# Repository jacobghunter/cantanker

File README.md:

This is a split wireless keyboard running ZMK with custom PCB and case designs

## Tools/software Used:
- [Ergogen](https://github.com/ergogen/ergogen) for layout and PCB generation as well as DXF files for case design
- [KiCad](https://www.kicad.org/) to wire the PCB
- [FreeCAD](https://www.freecad.org/) for case and plate design
- [ZMK](https://zmk.dev/) for the wireless firmware
- A slightly modified version of [this](https://github.com/AYM1607/zmk-driver-azoteq-iqs5xx) trackpad firmware by AYM1607

A big thank you to all the awesome people who have contributed to these projects, all of this being free and open source is truly amazing!

Its main features are:
- Bluetooth low energy connectivity
- Azotec TPS43 trackpad mounted on the right side
- 5000mAh batteries in each side
- Dual rotary encoders
- Nice! View display
- Low profile with choc v1 switches

## PCB Renders
| Side | Top | Bottom |
| :--- | :---: | :---: |
| **Left Half** |  |  |
| **Right Half** |  |  |

You can find the source FCStd file for the case and plates [here](mechanical/Cantanker_Case_and_Plates.FCStd) and print-ready exports below:
| Part | STLs | STEPs |
| :--- | :--- | :--- |
| **Left Case** | [Download](mechanical/exports/Cantanker_Left_Case.stl) | [Download](mechanical/exports/Cantanker_Left_Case.step) |
| **Right Case** | [Download](mechanical/exports/Cantanker_Right_Case.stl) | [Download](mechanical/exports/Cantanker_Right_Case.step) |
| **Left Plate** | [Download](mechanical/exports/Cantanker_Left_Plate.stl) | [Download](mechanical/exports/Cantanker_Left_Plate.step) |
| **Right Plate** | [Download](mechanical/exports/Cantanker_Right_Plate.stl) | [Download](mechanical/exports/Cantanker_Right_Plate.step) |

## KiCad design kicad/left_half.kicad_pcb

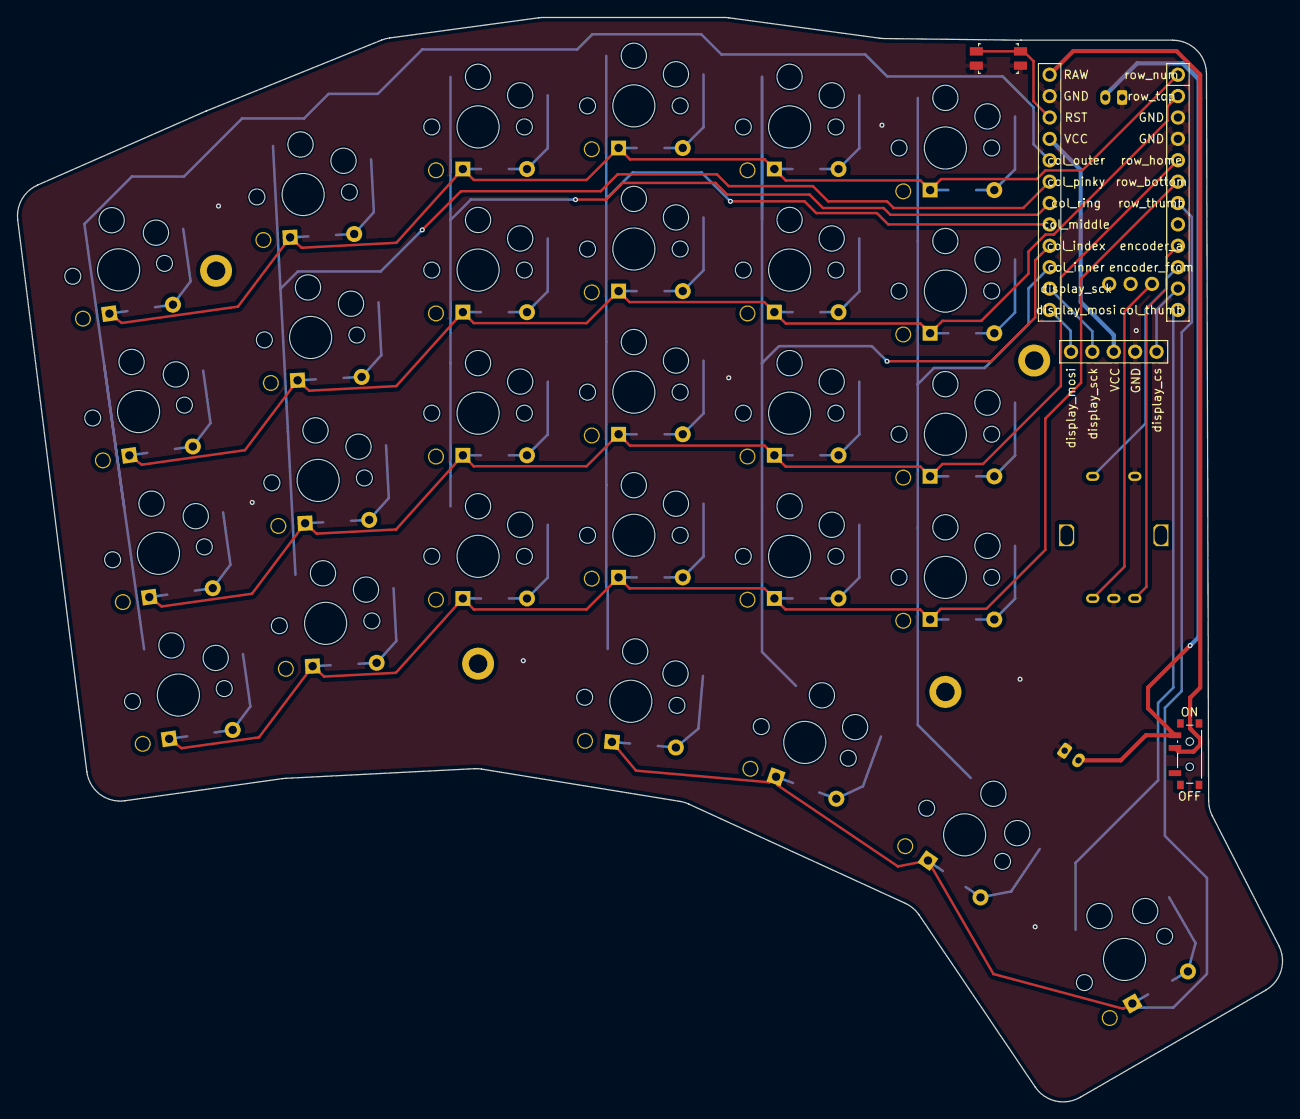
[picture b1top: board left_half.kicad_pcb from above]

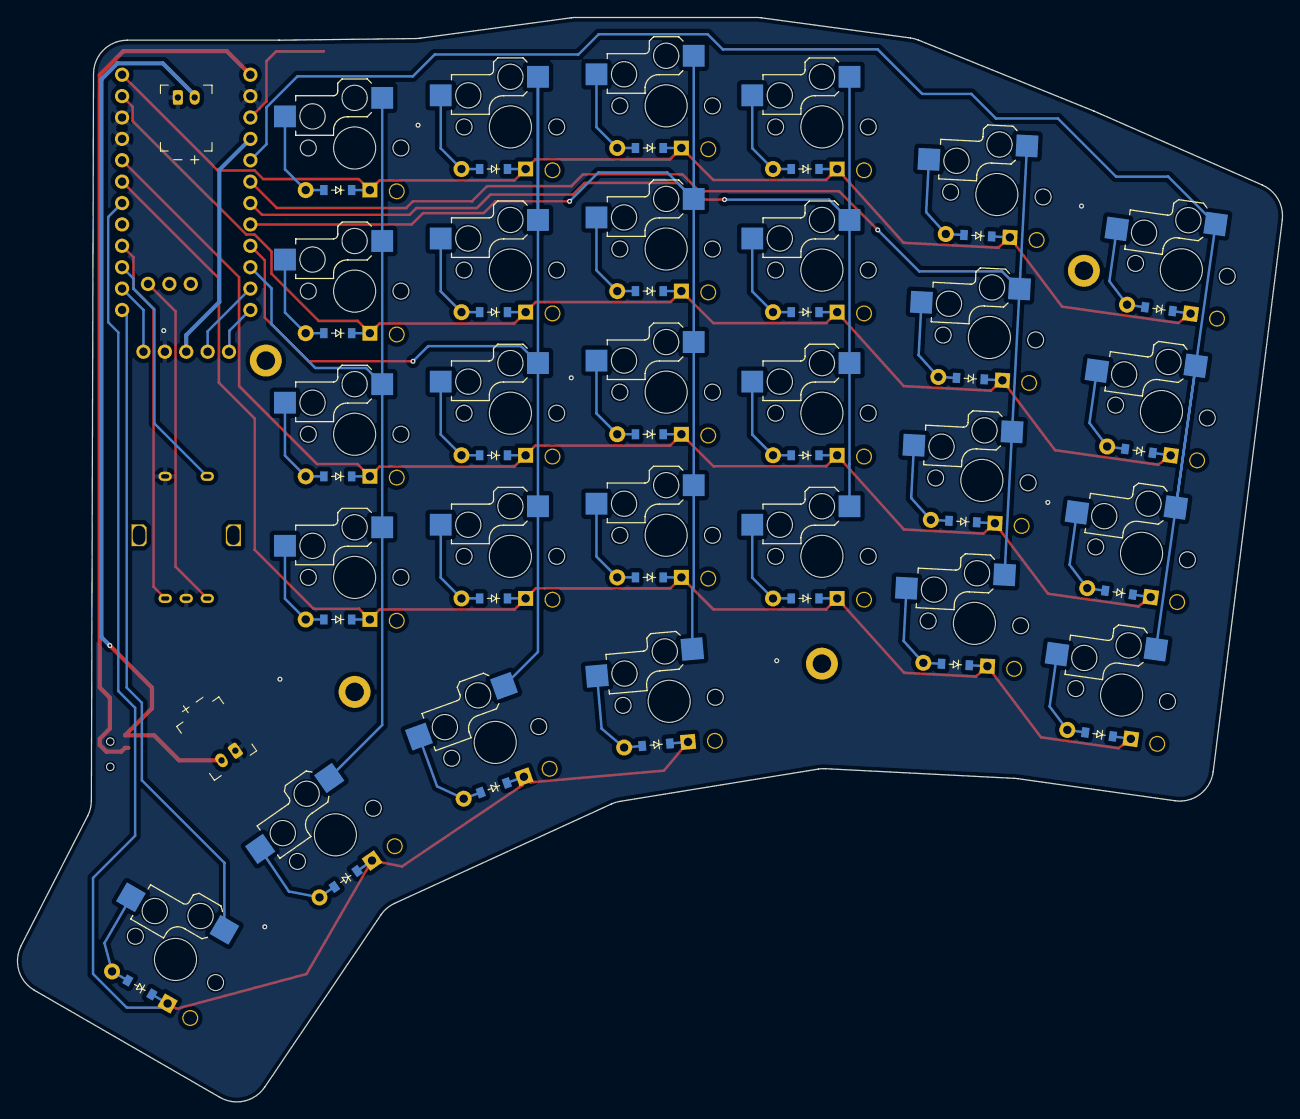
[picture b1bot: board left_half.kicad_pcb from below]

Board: 2 copper layers, 150.2 x 128.8 mm, 67 parts (58 on the bottom side), 51 nets.

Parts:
D1, D2, D3, D4, D5, D6, D7, D8, D9, D10, D11, D12, D13, D14, D15, D16, D17, D18, D19, D20, D21, D22, D23, D24, D25, D26, D27, D28: diode_tht_sod123
DISP1: display_nice_view
H1, H2, H3, H4: mounting_hole_plated
JST1, JST2: battery_connector_jst_ph_2
MCU1: mcu_supermini_nrf52840
PWR1: power_switch_smd_side
RE1: rotary_encoder_ec11_ec12
RST1: reset_switch_smd_side
S1, S2, S3, S4, S5, S6, S7, S8, S9, S10, S11, S12, S13, S14, S15, S16, S17, S18, S19, S20, S21, S22, S23, S24, S25, S26, S27, S28: switch_choc_v1_v2

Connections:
BAT_P: JST1.2, JST2.2, PWR1.3
GND: DISP1.4, JST1.1, JST2.1, MCU1.3, MCU1.4, MCU1.23, RE1.B, RE1.S2, RST1.2, RST1.4
RAW: MCU1.24, PWR1.2
RST: MCU1.22, RST1.1, RST1.3
VCC: DISP1.3, MCU1.21
col_index: MCU1.16, S17.1, S18.1, S19.1, S20.1, S28.1
col_inner: MCU1.15, S21.1, S22.1, S23.1, S24.1, S25.1
col_middle: MCU1.17, S13.1, S14.1, S15.1, S16.1, S27.1
col_outer: MCU1.20, S1.1, S2.1, S3.1, S4.1
col_pinky: MCU1.19, S5.1, S6.1, S7.1, S8.1
col_ring: MCU1.18, S9.1, S10.1, S11.1, S12.1
col_thumb: MCU1.12, S26.1
default_default: D28.2, S28.2
display_cs: DISP1.5, MCU1.11
display_mosi: DISP1.1, MCU1.13
display_sck: DISP1.2, MCU1.14
encoder_a: MCU1.9, RE1.A
encoder_b: MCU1.25, RE1.C
encoder_from: MCU1.10, RE1.S1
index_bottom: D17.2, S17.2
index_home: D18.2, S18.2
index_num: D20.2, S20.2
index_top: D19.2, S19.2
inner_bottom: D21.2, S21.2
inner_home: D22.2, S22.2
inner_num: D24.2, S24.2
inner_top: D23.2, S23.2
layer_cluster: D25.2, S25.2
middle_bottom: D13.2, S13.2
middle_home: D14.2, S14.2
middle_mod_default: D27.2, S27.2
middle_num: D16.2, S16.2
middle_top: D15.2, S15.2
outer_bottom: D1.2, S1.2
outer_home: D2.2, S2.2
outer_num: D4.2, S4.2
outer_top: D3.2, S3.2
pinky_bottom: D5.2, S5.2
pinky_home: D6.2, S6.2
pinky_num: D8.2, S8.2
pinky_top: D7.2, S7.2
ring_bottom: D9.2, S9.2
ring_home: D10.2, S10.2
ring_num: D12.2, S12.2
ring_top: D11.2, S11.2
row_bottom: D1.1, D5.1, D9.1, D13.1, D17.1, D21.1, MCU1.6
row_home: D2.1, D6.1, D10.1, D14.1, D18.1, D22.1, MCU1.5
row_num: D4.1, D8.1, D12.1, D16.1, D20.1, D24.1, MCU1.1
row_thumb: D25.1, D26.1, D27.1, D28.1, MCU1.7
row_top: D3.1, D7.1, D11.1, D15.1, D19.1, D23.1, MCU1.2
space_cluster: D26.2, S26.2

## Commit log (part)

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2025-10-21 Initial User Config.
2025-11-09 Add initial board configuration in YAML format
2025-11-11 update config
2025-11-11 Remove nav key
2025-11-11 update with removed nav key
2025-11-13 Final config?
2025-11-13 Align side of PCB
2025-11-15 update tags and add oled to both sides
2025-11-16 updating spacebar position
2025-11-16 final spacing changes
2025-11-16 updated config
2025-11-16 through holes for smd diodes
2025-11-16 diodes correct
2025-11-16 pcb update
2025-11-16 nearly done, removed jst connectors and fixed pin layout
2025-11-16 small changes
2025-11-17 added jst connectors back
2025-11-18 Move power switches away from edge
2025-11-20 slightly more spread so keys dont collide
2025-11-30 added ZMK configuration
2025-11-30 sofle added, wiring custom overlay for board
2025-12-02 fixed capital B in encoder definition for left MCU
2025-12-02 added net definition to one of the mod keys via a column to prevent ghost connection
2025-12-03 final ordered pcb
2025-12-12 added case and switch plate
2025-12-12 encoder cutout on plate
2025-12-13 update case
2025-12-13 case wrong
2025-12-16 case updates
2026-01-20 update outlines to have non-widened plate and bottom
2026-01-22 Update plate for freecad
2026-03-15 add shield and trackpad submodules
2026-03-15 add helpful files from shield repo to parent
2026-03-15 submodule tracking via github actions
2026-03-15 add kicad files
2026-03-15 kibot in github actions
2026-03-15 update kibot config
2026-03-15 add freecad file and exports
2026-03-15 update kibot config + readme
2026-03-15 add config to kibot
2026-03-15 fix readme
2026-03-15 update readme table headers
2026-03-15 add kibot config file
2026-03-15 update readme, fix kibot action
2026-03-15 update readme
    Added a thank you note for contributors and clarified keyboard description.
2026-03-15 kibot action push renders to repo
2026-03-15 docs: update pcb renders for right_half [skip ci]
2026-03-15 docs: update pcb renders for left_half [skip ci]
2026-03-15 put pcb renders in readme
2026-03-15 fix kibot export filenames
2026-03-15 remove duplicate docs images
2026-03-15 update pcb render images
2026-03-15 update pcb render table
2026-03-15 add new dependency module for gestures
2026-03-16 remove gestures module
2026-03-18 update TODO
2026-03-19 chore: update submodules to latest master
2026-03-26 update image
    Updated image in README and removed the old one.
2026-04-01 comment in todo
2026-04-05 new bluetooth settings
2026-04-12 new images of case
